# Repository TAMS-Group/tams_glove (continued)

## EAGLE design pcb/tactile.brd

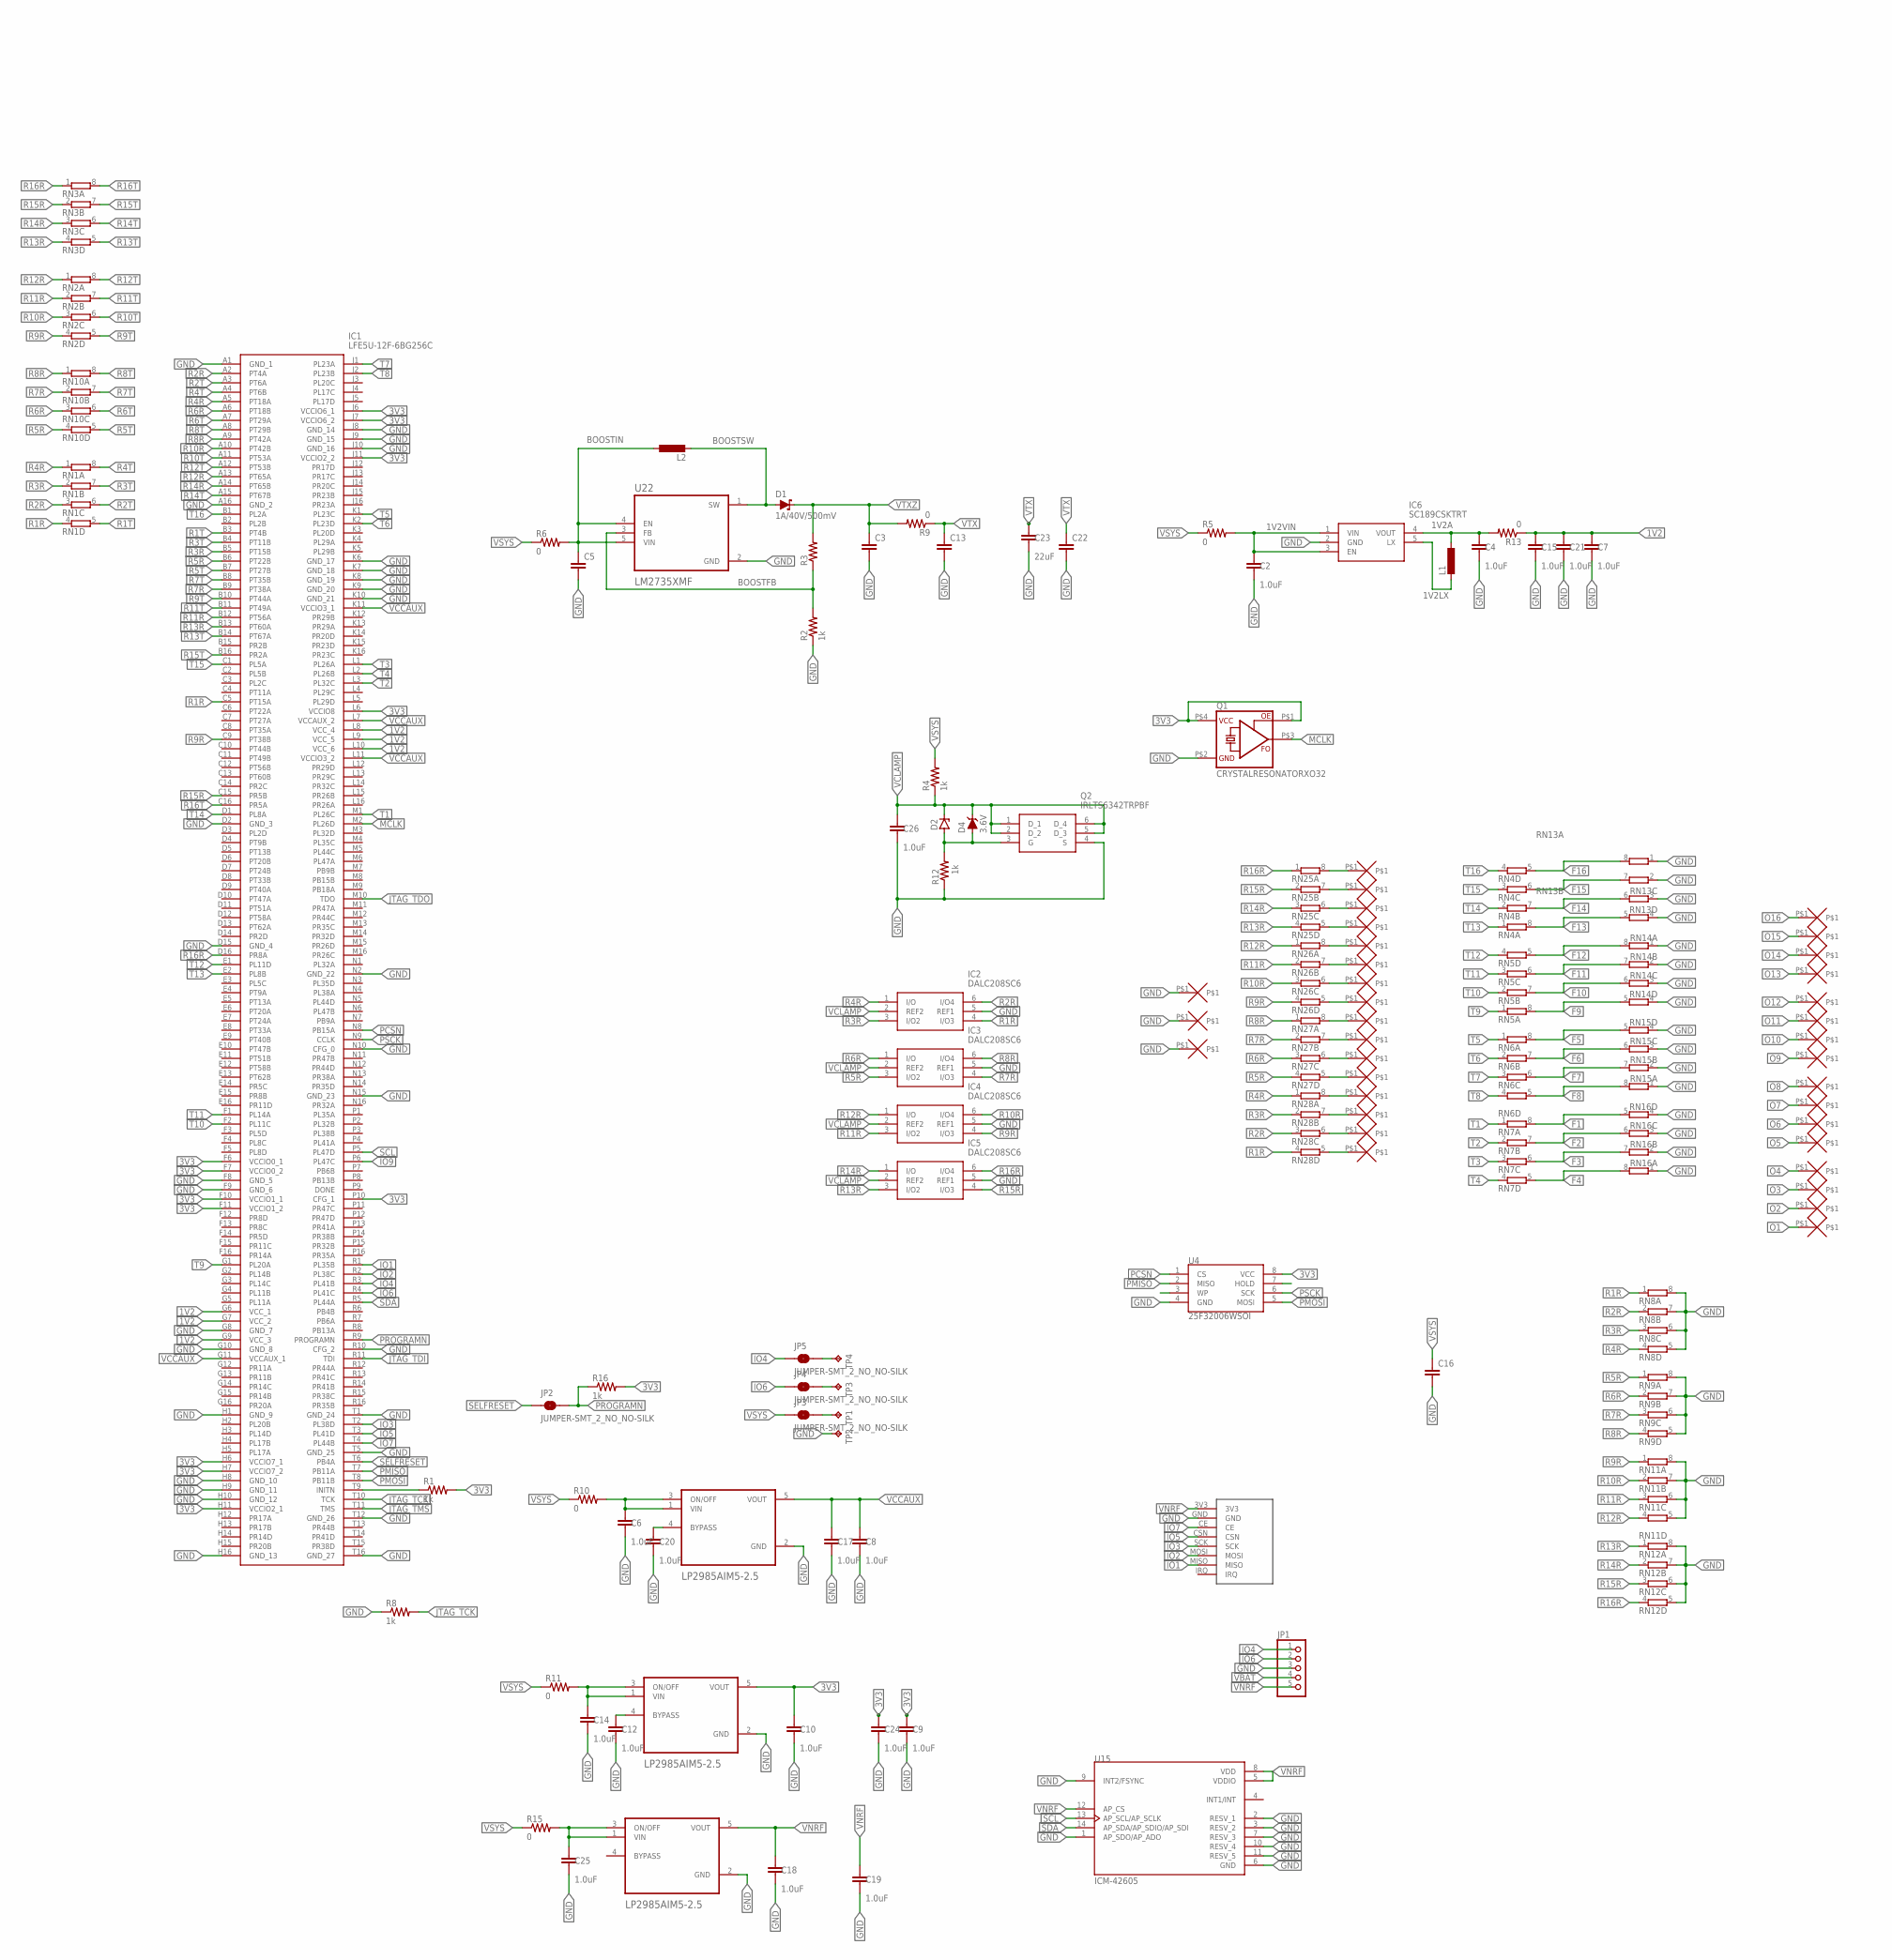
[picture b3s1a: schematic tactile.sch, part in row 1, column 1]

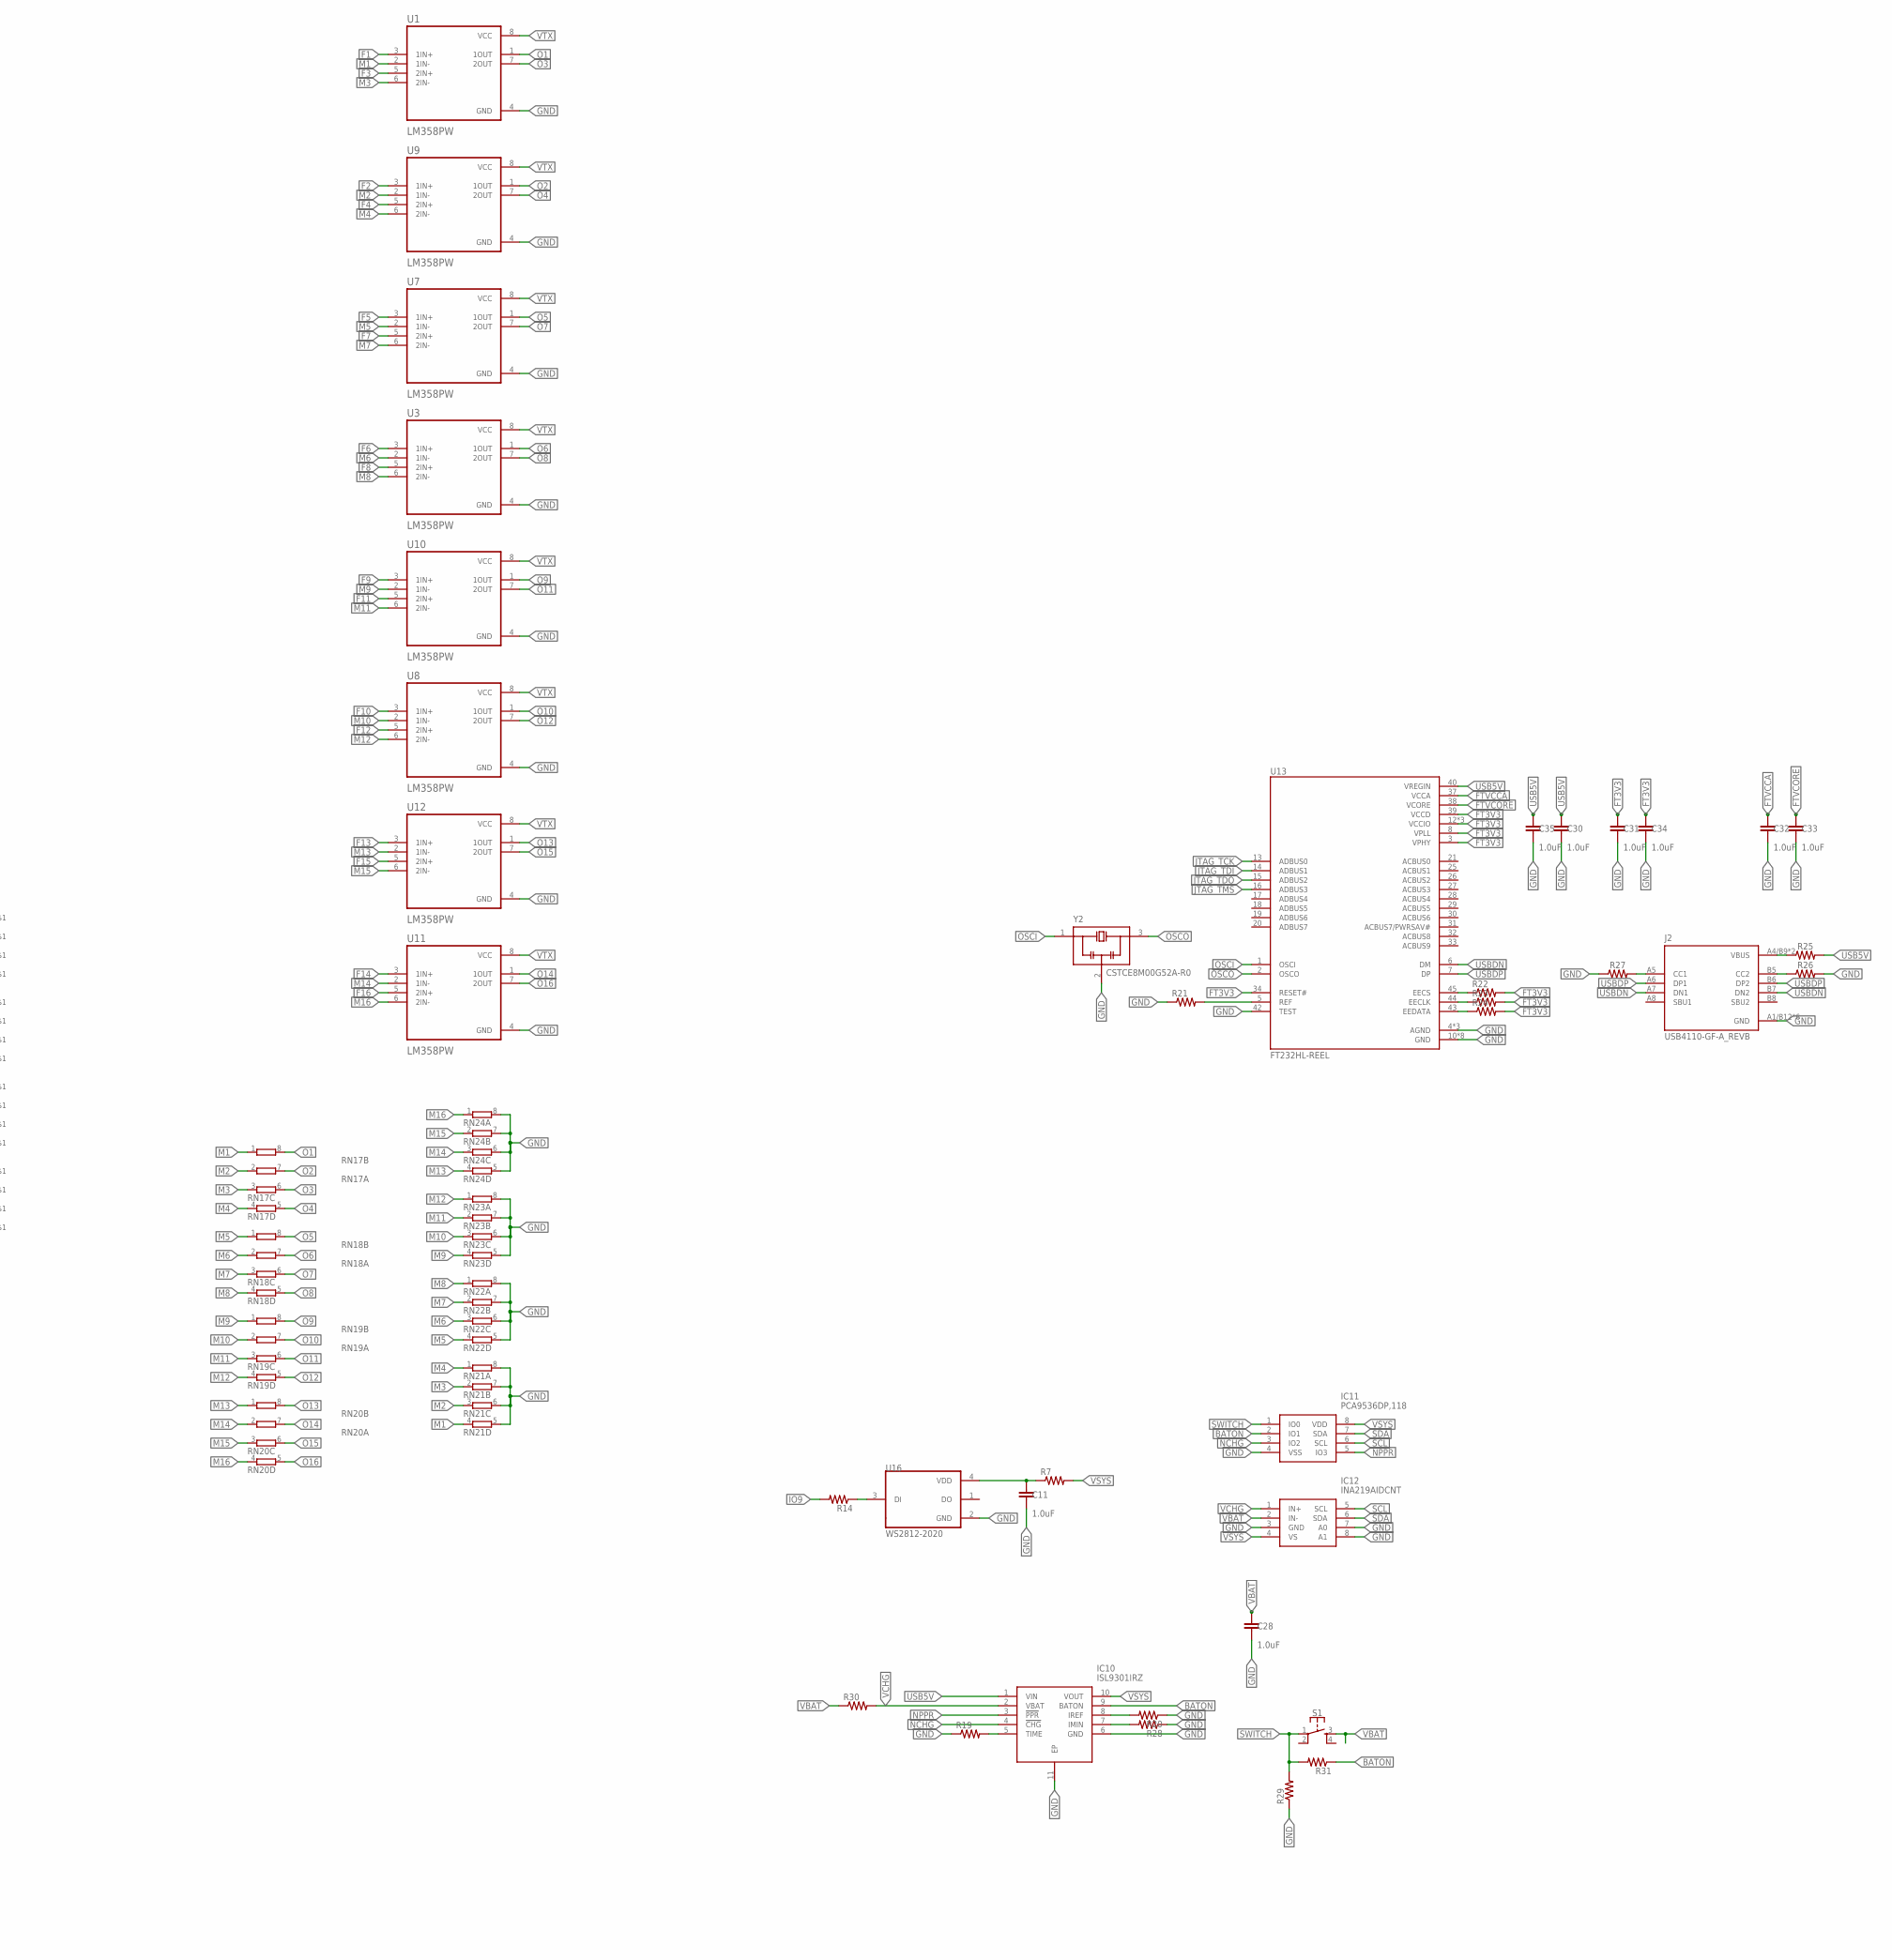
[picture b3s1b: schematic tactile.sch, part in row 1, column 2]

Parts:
C2, C4, C6, C7, C8, C9, C10, C11, C12, C14, C15, C17, C18, C19, C20, C21, C24, C25, C26, C28, C31, C32, C33, C34, C35: 1.0uF; 0603
C3, C5, C13, C22: C-EUC0805; C0805
C16: C-EUC1812; C1812
C23: 22uF; 0805
C30: 1.0uF; 1206
D1: 1A/40V/500mV; SMA-DIODE
D2: ZENER-DIODESOT23; SOT23
D4: 3.6V; SOD-323
IC1: LFE5U-12F-6BG256C; BGA256C80P16X16_1400X1400X170
IC2, IC3, IC4, IC5: DALC208SC6; SOT95P280X145-6N
IC6: SC189CSKTRT; SOT95P280X145-5N
IC10: ISL9301IRZ; SON50P300X300X90-11N
IC11: PCA9536DP,118; SOP65P490X110-8N
IC12: INA219AIDCNT; SOT65P280X145-8N
J2: USB4110-GF-A_REVB; GCT_USB4110-GF-A_REVB
JP1: PINHD-1X5M; 1X05M
JP2, JP3, JP4, JP5: JUMPER-SMT_2_NO_NO-SILK; SMT-JUMPER_2_NO_NO-SILK
L1: L-EUL3230M; L3230M
L2: L-EUL3225P; L3225P
Q1: CRYSTALRESONATORXO32; XO32
Q2: IRLTS6342TRPBF; SOT95P280X145-6N
R1, R2, R3, R4, R8, R12, R16: 1k; 0603
R5, R6, R9, R10, R11, R13, R15: 0; 0603
R7, R14, R19, R20, R21, R22, R23, R24, R25, R26, R27, R28, R29, R30, R31: 0603
RN1, RN2, RN3, RN4, RN5, RN6, RN7, RN8, RN9, RN10, RN11, RN12, RN13, RN14, RN15, RN16, RN17, RN18, RN19, RN20, RN21, RN22, RN23, RN24, RN25, RN26, RN27, RN28: 4R-NEXBV8V; EXBV8V
S1: MOMENTARY-SWITCH-SPST-2-SMD-5.2MM; TACTILE_SWITCH_SMD_5.2MM
TP1, TP2, TP3, TP4: TPTP12SQ; TP12SQ
U1, U3, U7, U8, U9, U10, U11, U12: LM358PW; SOP65P640X120-8N
U4: 25F32006WSOI; SO08-EIAJ
U5, U6, U14: LP2985AIM5-2.5; SOT95P280X145-5N
U13: FT232HL-REEL; QFP50P900X900X160-48N
U15: ICM-42605; PQFN50P300X250X97-14N
U16: WS2812-2020; LED_WS2812-2020
U22: LM2735XMF; SOT95P280X145-5N
U$1, U$2, U$3, U$4, U$5, U$6, U$7, U$8, U$10, U$11, U$12, U$13, U$14, U$15, U$16, U$17, U$18, U$19, U$20, U$21, U$22, U$23, U$24, U$25, U$26, U$27, U$28, U$29, U$30, U$31, U$32, U$33, U$34, U$35, U$36: PADPAD3X05; PAD3X05
U$9: NRF24MODULE; NRF24SMT
Y2: CSTCE8M00G52A-R0; OSC_CSTCE8M00G52A-R0

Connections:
1V2: C7.1, C15.1, C21.1, IC1.G6 (VCC_1), IC1.G7 (VCC_2), IC1.G9 (VCC_3), IC1.L8 (VCC_4), IC1.L9 (VCC_5), IC1.L10 (VCC_6), R13.1
1V2A: C4.1, IC6.4 (VOUT), L1.1, R13.2
1V2LX: IC6.5 (LX), L1.2
1V2VIN: C2.1, IC6.1 (VIN), IC6.3 (EN), R5.2
3V3: C9.1, C10.1, C24.1, IC1.F6 (VCCIO0_1), IC1.F7 (VCCIO0_2), IC1.F10 (VCCIO1_1), IC1.F11 (VCCIO1_2), IC1.H6 (VCCIO7_1), IC1.H7 (VCCIO7_2), IC1.H11 (VCCIO2_1), IC1.J6 (VCCIO6_1), IC1.J7 (VCCIO6_2), IC1.J11 (VCCIO2_2), IC1.L6 (VCCIO8), IC1.P10 (CFG_1), Q1.P$1 (OE), Q1.P$4 (VCC), R1.2, R16.2, U4.8 (VCC), U6.5 (VOUT)
BATON: IC10.9 (BATON), IC11.2 (IO1), R31.1
BOOSTFB: R2.2, R3.1, U22.3 (FB)
BOOSTIN: C5.1, L2.1, R6.2, U22.4 (EN), U22.5 (VIN)
BOOSTSW: D1.A, L2.2, U22.1 (SW)
F1: RN7.8 (2), RN16.5 (2), U1.3 (1IN+)
F2: RN7.7 (2), RN16.6 (2), U9.3 (1IN+)
F3: RN7.6 (2), RN16.7 (2), U1.5 (2IN+)
F4: RN7.5 (2), RN16.8 (2), U9.5 (2IN+)
F5: RN6.8 (2), RN15.5 (2), U7.3 (1IN+)
F6: RN6.7 (2), RN15.6 (2), U3.3 (1IN+)
F7: RN6.6 (2), RN15.7 (2), U7.5 (2IN+)
F8: RN6.5 (2), RN15.8 (2), U3.5 (2IN+)
F9: RN5.8 (2), RN14.5 (2), U10.3 (1IN+)
F10: RN5.7 (2), RN14.6 (2), U8.3 (1IN+)
F11: RN5.6 (2), RN14.7 (2), U10.5 (2IN+)
F12: RN5.5 (2), RN14.8 (2), U8.5 (2IN+)
F13: RN4.8 (2), RN13.5 (2), U12.3 (1IN+)
F14: RN4.7 (2), RN13.6 (2), U11.3 (1IN+)
F15: RN4.6 (2), RN13.7 (2), U12.5 (2IN+)
F16: RN4.5 (2), RN13.8 (2), U11.5 (2IN+)
FT3V3: C31.1, C34.1, R22.2, R23.2, R24.2, U13.3 (VPHY), U13.8 (VPLL), U13.12 (VCCIO), U13.24 (VCCIO), U13.34 (RESET#), U13.39 (VCCD), U13.46 (VCCIO)
FTVCCA: C32.1, U13.37 (VCCA)
FTVCORE: C33.1, U13.38 (VCORE)
GND: C2.2, C3.2, C4.2, C5.2, C6.2, C7.2, C8.2, C9.2, C10.2, C11.2, C12.2, C13.2, C14.2, C15.2, C16.2, C17.2, C18.2, C19.2, C20.2, C21.2, C22.2, C23.2, C24.2, C25.2, C26.2, C28.2, C30.2, C31.2, C32.2, C33.2, C34.2, C35.2, IC1.A1 (GND_1), IC1.A16 (GND_2), IC1.D2 (GND_3), IC1.D15 (GND_4), IC1.F8 (GND_5), IC1.F9 (GND_6), IC1.G8 (GND_7), IC1.G10 (GND_8), IC1.H1 (GND_9), IC1.H8 (GND_10), IC1.H9 (GND_11), IC1.H10 (GND_12), IC1.H16 (GND_13), IC1.J8 (GND_14), IC1.J9 (GND_15), IC1.J10 (GND_16), IC1.K6 (GND_17), IC1.K7 (GND_18), IC1.K8 (GND_19), IC1.K9 (GND_20), IC1.K10 (GND_21), IC1.N2 (GND_22), IC1.N10 (CFG_0), IC1.N15 (GND_23), IC1.R10 (CFG_2), IC1.T1 (GND_24), IC1.T5 (GND_25), IC1.T12 (GND_26), IC1.T16 (GND_27), IC2.5 (REF1), IC3.5 (REF1), IC4.5 (REF1), IC5.5 (REF1), IC6.2 (GND), IC10.6 (GND), IC10.11 (EP), IC11.4 (VSS), IC12.3 (GND), IC12.7 (A0), IC12.8 (A1), J2.A1/B12 (GND), J2.B1/A12 (GND), J2.S1 (GND), J2.S2 (GND), J2.S3 (GND), J2.S4 (GND), JP1.3, Q1.P$2 (GND), Q2.4 (S), R2.1, R8.1, R12.1, R19.1, R20.1, R21.1, R26.2, R27.1, R28.1, R29.1, RN8.5 (2), RN8.6 (2), RN8.7 (2), RN8.8 (2), RN9.5 (2), RN9.6 (2), RN9.7 (2), RN9.8 (2), RN11.5 (2), RN11.6 (2), RN11.7 (2), RN11.8 (2), RN12.5 (2), RN12.6 (2), RN12.7 (2), RN12.8 (2), RN13.1, RN13.2 (1), RN13.3 (1), RN13.4 (1), RN14.1, RN14.2 (1), RN14.3 (1), RN14.4 (1), RN15.1, RN15.2 (1), RN15.3 (1), RN15.4 (1), RN16.1, RN16.2 (1), RN16.3 (1), RN16.4 (1), RN21.5 (2), RN21.6 (2), RN21.7 (2), RN21.8 (2), RN22.5 (2), RN22.6 (2), RN22.7 (2), RN22.8 (2), RN23.5 (2), RN23.6 (2), RN23.7 (2), RN23.8 (2), RN24.5 (2), RN24.6 (2), RN24.7 (2), RN24.8 (2), TP2.TP, U1.4 (GND), U3.4 (GND), U4.4 (GND), U5.2 (GND), U6.2 (GND), U7.4 (GND), U8.4 (GND), U9.4 (GND), U10.4 (GND), U11.4 (GND), U12.4 (GND), U13.4 (AGND), U13.9 (AGND), U13.10 (GND), U13.11 (GND), U13.22 (GND), U13.23 (GND), U13.35 (GND), U13.36 (GND), U13.41 (AGND), U13.42 (TEST), U13.47 (GND), U13.48 (GND), U14.2 (GND), U15.1 (AP_SDO/AP_ADO), U15.2 (RESV_1), U15.3 (RESV_2), U15.6 (GND), U15.7 (RESV_3), U15.9 (INT2/FSYNC), U15.10 (RESV_4), U15.11 (RESV_5), U16.2 (GND), U22.2 (GND), U$1.P$1, U$9.GND, U$35.P$1, U$36.P$1, Y2.2 (GND)
IO1: IC1.R1 (PL35B), U$9.MISO
IO2: IC1.R2 (PL38C), U$9.MOSI
IO3: IC1.T2 (PL38D), U$9.SCK
IO4: IC1.R3 (PL41B), JP1.1, JP5.1
IO5: IC1.T3 (PL41D), U$9.CSN
IO6: IC1.R4 (PL41C), JP1.2, JP4.1
IO7: IC1.T4 (PL44B), U$9.CE
IO9: IC1.P6 (PL47C), R14.2
JTAG_TCK: IC1.T10 (TCK), R8.2, U13.13 (ADBUS0)
JTAG_TDI: IC1.R11 (TDI), U13.14 (ADBUS1)
JTAG_TDO: IC1.M10 (TDO), U13.15 (ADBUS2)
JTAG_TMS: IC1.T11 (TMS), U13.16 (ADBUS3)
M1: RN17.1, RN21.4 (1), U1.2 (1IN-)
M2: RN17.2 (1), RN21.3 (1), U9.2 (1IN-)
M3: RN17.3 (1), RN21.2 (1), U1.6 (2IN-)
M4: RN17.4 (1), RN21.1, U9.6 (2IN-)
M5: RN18.1, RN22.4 (1), U7.2 (1IN-)
M6: RN18.2 (1), RN22.3 (1), U3.2 (1IN-)
M7: RN18.3 (1), RN22.2 (1), U7.6 (2IN-)
M8: RN18.4 (1), RN22.1, U3.6 (2IN-)
M9: RN19.1, RN23.4 (1), U10.2 (1IN-)
M10: RN19.2 (1), RN23.3 (1), U8.2 (1IN-)
M11: RN19.3 (1), RN23.2 (1), U10.6 (2IN-)
M12: RN19.4 (1), RN23.1, U8.6 (2IN-)
M13: RN20.1, RN24.4 (1), U12.2 (1IN-)
M14: RN20.2 (1), RN24.3 (1), U11.2 (1IN-)
M15: RN20.3 (1), RN24.2 (1), U12.6 (2IN-)
M16: RN20.4 (1), RN24.1, U11.6 (2IN-)
MCLK: IC1.M2 (PL26D), Q1.P$3 (FO)
unnamed: RN25.8 (2), U$18.P$1
unnamed: IC10.5 (TIME), R19.2
unnamed: IC10.8 (IREF), R20.2
unnamed: IC1.T9 (INITN), R1.1
unnamed: RN25.7 (2), U$17.P$1
unnamed: RN25.6 (2), U$16.P$1
unnamed: RN25.5 (2), U$15.P$1
unnamed: RN26.5 (2), U$11.P$1
unnamed: RN26.6 (2), U$12.P$1
unnamed: RN26.7 (2), U$13.P$1
unnamed: RN26.8 (2), U$14.P$1
unnamed: RN27.5 (2), U$6.P$1
unnamed: RN27.6 (2), U$7.P$1
unnamed: RN27.7 (2), U$8.P$1
unnamed: RN27.8 (2), U$10.P$1
unnamed: RN28.5 (2), U$2.P$1
unnamed: RN28.6 (2), U$3.P$1
unnamed: RN28.7 (2), U$4.P$1
unnamed: RN28.8 (2), U$5.P$1
unnamed: C12.1, U6.4 (BYPASS)
unnamed: IC10.7 (IMIN), R28.2
unnamed: C11.1, R7.1, U16.4 (VDD)
unnamed: R14.1, U16.3 (DI)
unnamed: D2.1 (A), D4.A, Q2.3 (G), R12.2
unnamed: C20.1, U5.4 (BYPASS)
unnamed: C6.1, R10.2, U5.1 (VIN), U5.3 (ON/OFF)
unnamed: JP3.2, TP1.TP
unnamed: C14.1, R11.2, U6.1 (VIN), U6.3 (ON/OFF)
unnamed: C25.1, R15.2, U14.1 (VIN), U14.3 (ON/OFF)
unnamed: JP4.2, TP3.TP
unnamed: JP5.2, TP4.TP
unnamed: R21.2, U13.5 (REF)
unnamed: R22.1, U13.45 (EECS)
unnamed: R23.1, U13.44 (EECLK)
unnamed: R24.1, U13.43 (EEDATA)
unnamed: J2.A5 (CC1), R27.2
unnamed: J2.B5 (CC2), R26.1
unnamed: J2.A4/B9 (VBUS), J2.B4/A9 (VBUS), R25.1
NCHG: IC10.4 (!CHG), IC11.3 (IO2)
NPPR: IC10.3 (!PPR), IC11.5 (IO3)
O1: RN17.8 (2), U1.1 (1OUT), U$20.P$1
O2: RN17.7 (2), U9.1 (1OUT), U$21.P$1
O3: RN17.6 (2), U1.7 (2OUT), U$19.P$1
O4: RN17.5 (2), U9.7 (2OUT), U$22.P$1
O5: RN18.8 (2), U7.1 (1OUT), U$23.P$1
O6: RN18.7 (2), U3.1 (1OUT), U$24.P$1
O7: RN18.6 (2), U7.7 (2OUT), U$25.P$1
O8: RN18.5 (2), U3.7 (2OUT), U$26.P$1
O9: RN19.8 (2), U10.1 (1OUT), U$27.P$1
O10: RN19.7 (2), U8.1 (1OUT), U$28.P$1
O11: RN19.6 (2), U10.7 (2OUT), U$29.P$1
O12: RN19.5 (2), U8.7 (2OUT), U$30.P$1
O13: RN20.8 (2), U12.1 (1OUT), U$31.P$1
O14: RN20.7 (2), U11.1 (1OUT), U$32.P$1
O15: RN20.6 (2), U12.7 (2OUT), U$33.P$1
O16: RN20.5 (2), U11.7 (2OUT), U$34.P$1
OSCI: U13.1 (OSCI), Y2.1 (IN)
OSCO: U13.2 (OSCO), Y2.3 (OUT)
PCSN: IC1.N8 (PB15A), U4.1 (CS)
PMISO: IC1.T7 (PB11A), U4.2 (MISO)
PMOSI: IC1.T8 (PB11B), U4.5 (MOSI)
PROGRAMN: IC1.R9 (PROGRAMN), JP2.2, R16.1
PSCK: IC1.N9 (CCLK), U4.6 (SCK)
R1R: IC1.C5 (PT15A), IC2.4 (I/O3), RN1.4 (1), RN8.1, RN28.4 (1)
R1T: IC1.B3 (PT4B), RN1.5 (2)
R2R: IC1.A2 (PT4A), IC2.6 (I/O4), RN1.3 (1), RN8.2 (1), RN28.3 (1)
R2T: IC1.A3 (PT6A), RN1.6 (2)
R3R: IC1.B5 (PT15B), IC2.3 (I/O2), RN1.2 (1), RN8.3 (1), RN28.2 (1)
R3T: IC1.B4 (PT11B), RN1.7 (2)
R4R: IC1.A5 (PT18A), IC2.1 (I/O), RN1.1, RN8.4 (1), RN28.1
R4T: IC1.A4 (PT6B), RN1.8 (2)
R5R: IC1.B6 (PT22B), IC3.3 (I/O2), RN9.1, RN10.4 (1), RN27.4 (1)
R5T: IC1.B7 (PT27B), RN10.5 (2)
R6R: IC1.A6 (PT18B), IC3.1 (I/O), RN9.2 (1), RN10.3 (1), RN27.3 (1)
R6T: IC1.A7 (PT29A), RN10.6 (2)
R7R: IC1.B9 (PT38A), IC3.4 (I/O3), RN9.3 (1), RN10.2 (1), RN27.2 (1)
R7T: IC1.B8 (PT35B), RN10.7 (2)
R8R: IC1.A9 (PT42A), IC3.6 (I/O4), RN9.4 (1), RN10.1, RN27.1
R8T: IC1.A8 (PT29B), RN10.8 (2)
R9R: IC1.C9 (PT38B), IC4.4 (I/O3), RN2.4 (1), RN11.1, RN26.4 (1)
R9T: IC1.B10 (PT44A), RN2.5 (2)
R10R: IC1.A10 (PT42B), IC4.6 (I/O4), RN2.3 (1), RN11.2 (1), RN26.3 (1)
R10T: IC1.A11 (PT53A), RN2.6 (2)
R11R: IC1.B12 (PT56A), IC4.3 (I/O2), RN2.2 (1), RN11.3 (1), RN26.2 (1)
R11T: IC1.B11 (PT49A), RN2.7 (2)
R12R: IC1.A13 (PT65A), IC4.1 (I/O), RN2.1, RN11.4 (1), RN26.1
R12T: IC1.A12 (PT53B), RN2.8 (2)
R13R: IC1.B13 (PT60A), IC5.3 (I/O2), RN3.4 (1), RN12.1, RN25.4 (1)
R13T: IC1.B14 (PT67A), RN3.5 (2)
R14R: IC1.A14 (PT65B), IC5.1 (I/O), RN3.3 (1), RN12.2 (1), RN25.3 (1)
R14T: IC1.A15 (PT67B), RN3.6 (2)
R15R: IC1.C15 (PR5B), IC5.4 (I/O3), RN3.2 (1), RN12.3 (1), RN25.2 (1)
R15T: IC1.B16 (PR2A), RN3.7 (2)
R16R: IC1.D16 (PR8A), IC5.6 (I/O4), RN3.1, RN12.4 (1), RN25.1
R16T: IC1.C16 (PR5A), RN3.8 (2)
SCL: IC1.P5 (PL47D), IC11.6 (SCL), IC12.5 (SCL), U15.13 (AP_SCL/AP_SCLK)
SDA: IC1.R5 (PL44A), IC11.7 (SDA), IC12.6 (SDA), U15.14 (AP_SDA/AP_SDIO/AP_SDI)
SELFRESET: IC1.T6 (PB4A), JP2.1
SWITCH: IC11.1 (IO0), R29.2, R31.2, S1.1
T1: IC1.M1 (PL26C), RN7.1
T2: IC1.L3 (PL32C), RN7.2 (1)
T3: IC1.L1 (PL26A), RN7.3 (1)
T4: IC1.L2 (PL26B), RN7.4 (1)
T5: IC1.K1 (PL23C), RN6.1
T6: IC1.K2 (PL23D), RN6.2 (1)
T7: IC1.J1 (PL23A), RN6.3 (1)
T8: IC1.J2 (PL23B), RN6.4 (1)
T9: IC1.G1 (PL20A), RN5.1
T10: IC1.F2 (PL11C), RN5.2 (1)
T11: IC1.F1 (PL14A), RN5.3 (1)
T12: IC1.E1 (PL11D), RN5.4 (1)
T13: IC1.E2 (PL8B), RN4.1
T14: IC1.D1 (PL8A), RN4.2 (1)
T15: IC1.C1 (PL5A), RN4.3 (1)
T16: IC1.B1 (PL2A), RN4.4 (1)
USB5V: C30.1, C35.1, IC10.1 (VIN), R25.2, U13.40 (VREGIN)
USBDN: J2.A7 (DN1), J2.B7 (DN2), U13.6 (DM)
USBDP: J2.A6 (DP1), J2.B6 (DP2), U13.7 (DP)
VBAT: C28.1, IC12.2 (IN-), JP1.4, R30.1, S1.3
VCCAUX: C8.1, C17.1, IC1.G11 (VCCAUX_1), IC1.K11 (VCCIO3_1), IC1.L7 (VCCAUX_2), IC1.L11 (VCCIO3_2), U5.5 (VOUT)
VCHG: IC10.2 (VBAT), IC12.1 (IN+), R30.2
VCLAMP: C26.1, D2.3 (C), D4.C, IC2.2 (REF2), IC3.2 (REF2), IC4.2 (REF2), IC5.2 (REF2), Q2.1 (D_1), Q2.2 (D_2), Q2.5 (D_3), Q2.6 (D_4), R4.1
VNRF: C18.1, C19.1, JP1.5, U14.5 (VOUT), U15.5 (VDDIO), U15.8 (VDD), U15.12 (AP_CS), U$9.3V3
VSYS: C16.1, IC10.10 (VOUT), IC11.8 (VDD), IC12.4 (VS), JP3.1, R4.2, R5.1, R6.1, R7.2, R10.1, R11.1, R15.1
VTX: C13.1, C22.1, C23.1, R9.1, U1.8 (VCC), U3.8 (VCC), U7.8 (VCC), U8.8 (VCC), U9.8 (VCC), U10.8 (VCC), U11.8 (VCC), U12.8 (VCC)
VTXZ: C3.1, D1.C, R3.2, R9.2

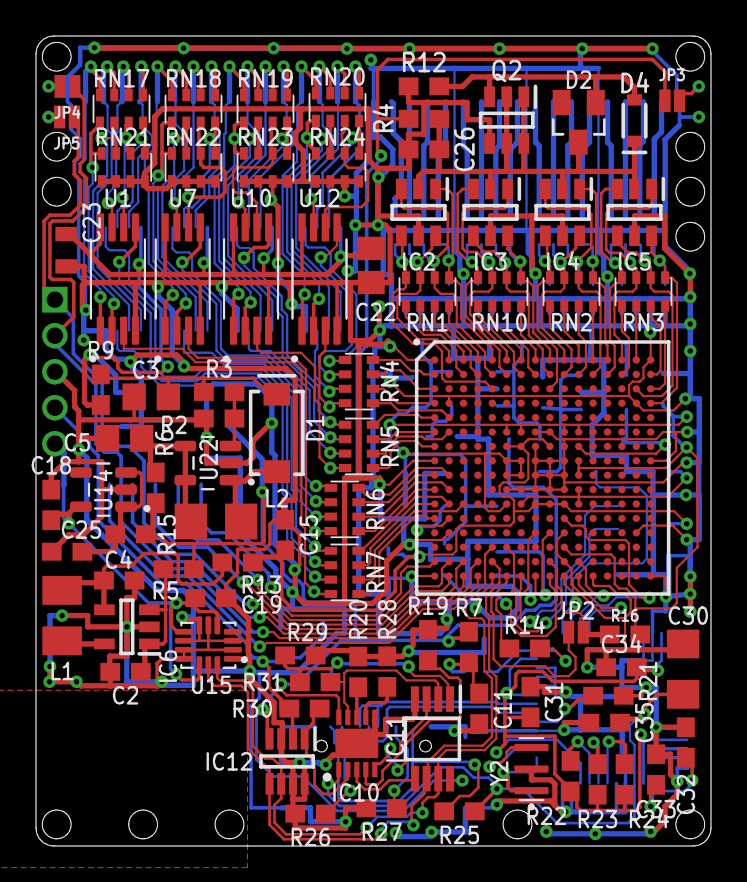
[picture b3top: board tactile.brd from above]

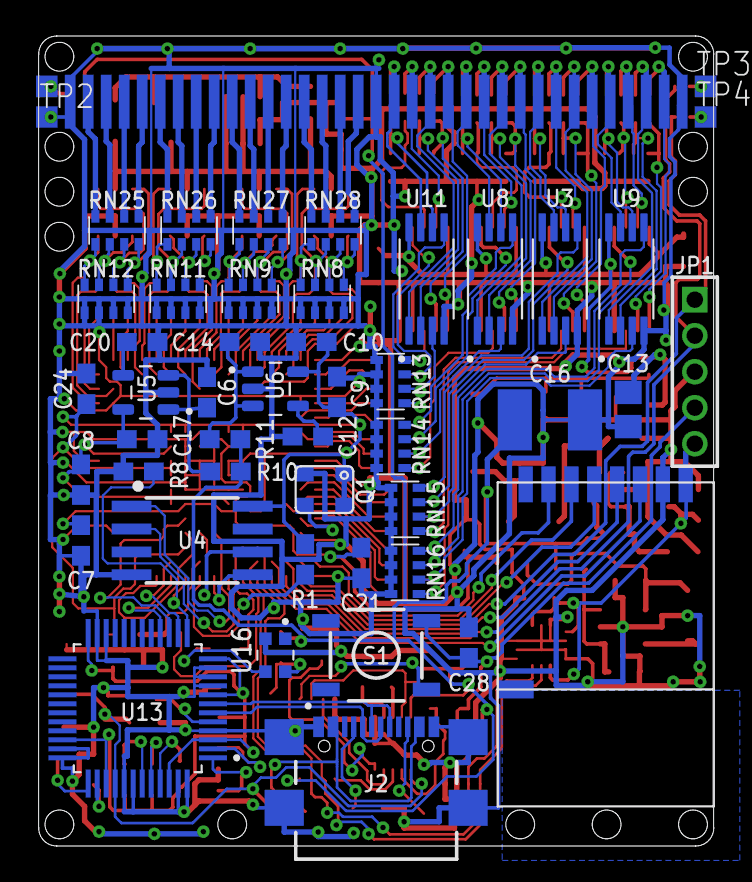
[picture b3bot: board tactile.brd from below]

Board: 2 copper layers, 37.5 x 45.0 mm, 169 parts (83 on the bottom side), 184 nets.
